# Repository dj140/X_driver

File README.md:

# X_driver
Base on odrive 3.5 sch

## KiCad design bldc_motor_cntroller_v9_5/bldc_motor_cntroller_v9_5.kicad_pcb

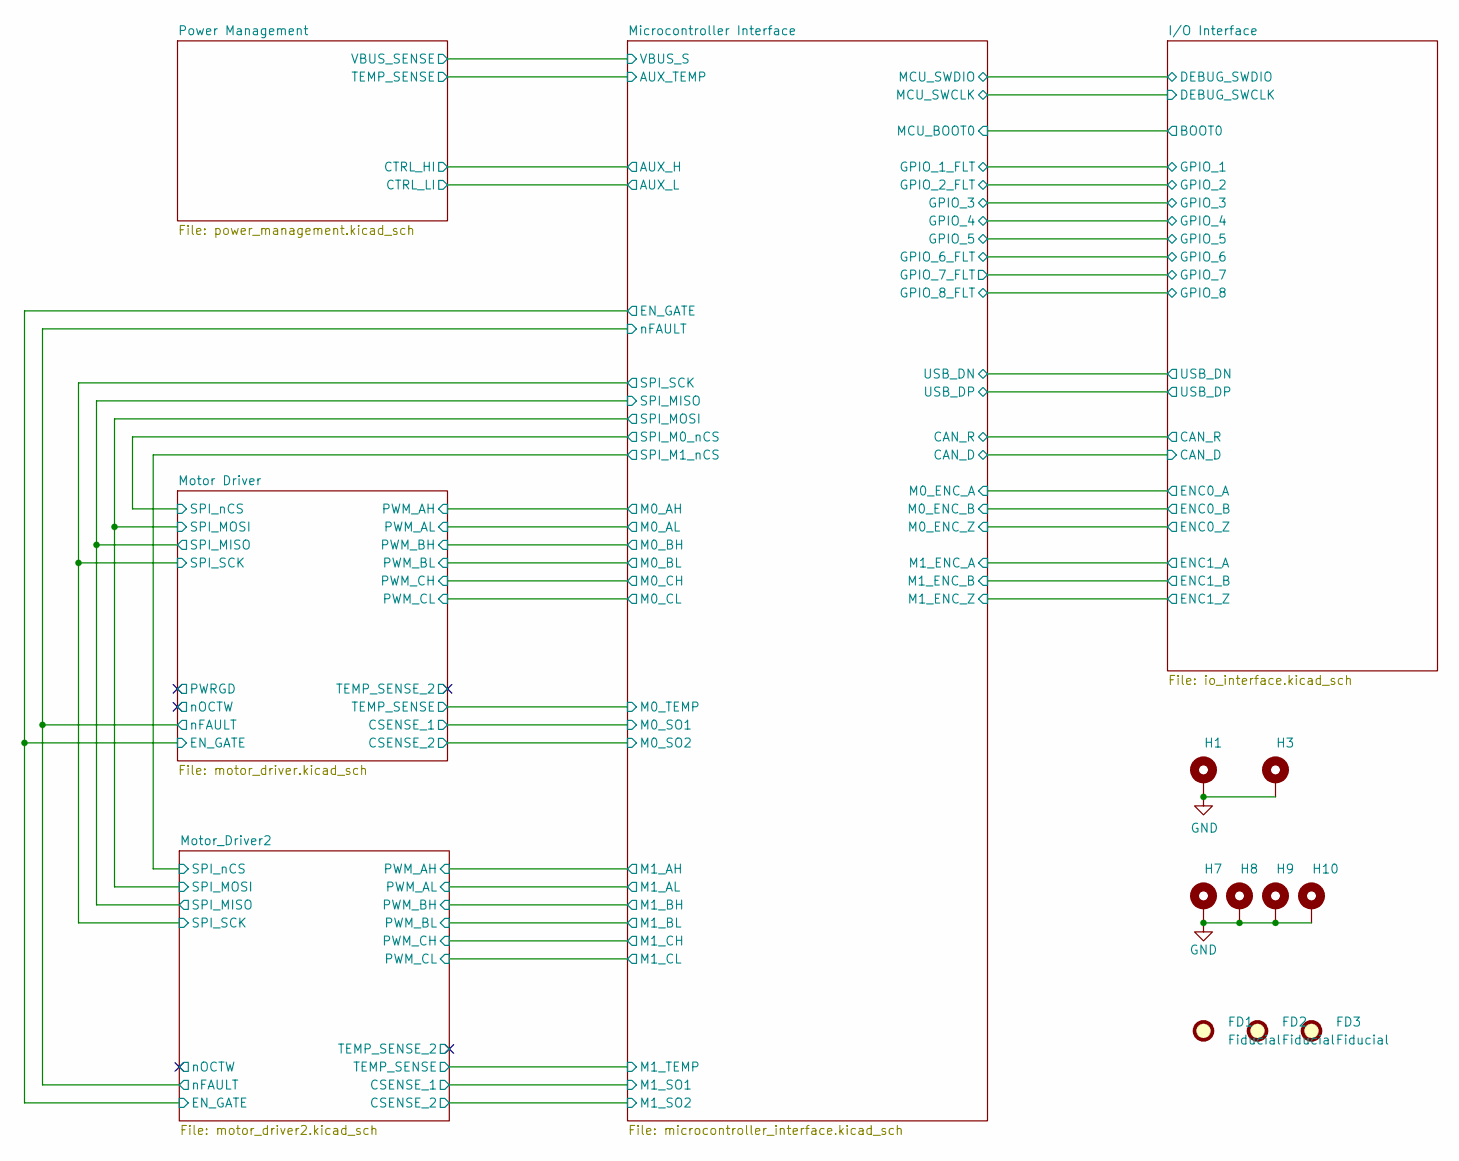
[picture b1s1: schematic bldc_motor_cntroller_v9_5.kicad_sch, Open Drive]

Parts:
FD1, FD2, FD3: Fiducial; Fiducial_1mm_Mask2mm
H1, H3: MountingHole_3.2mm_M3_Pad_Via
H7, H8, H9, H10: MountingHole_Pad; MountingHole_4.3mm_M4_Pad

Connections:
GND: H1.1, H3.1, H7.1, H8.1, H9.1, H10.1; also elsewhere on the board

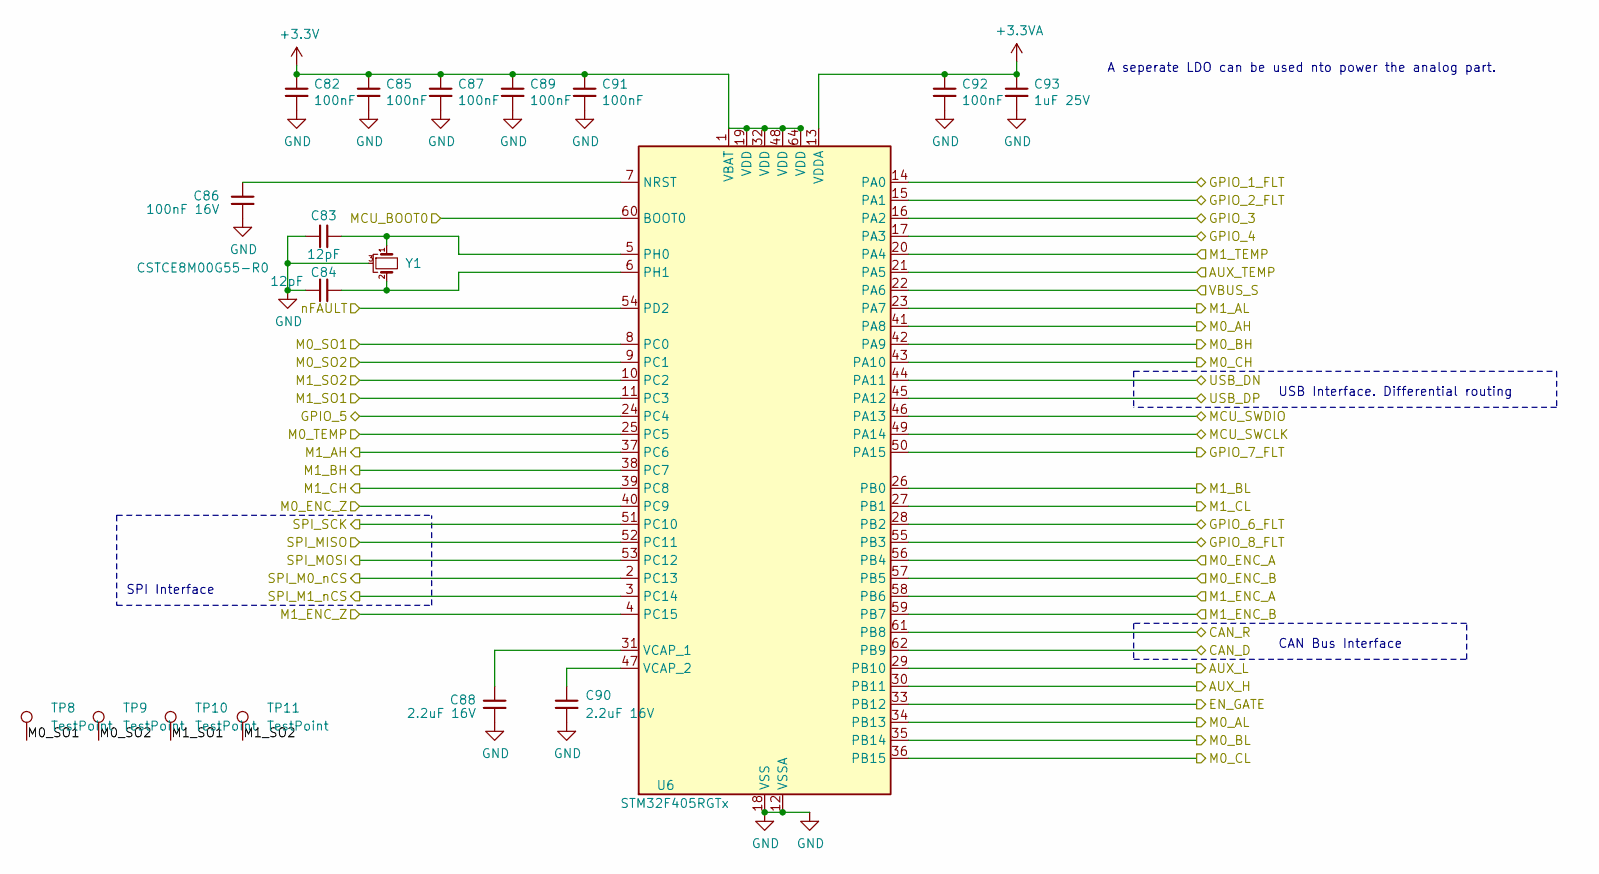
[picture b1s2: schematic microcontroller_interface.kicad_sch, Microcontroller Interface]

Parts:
C82, C85, C87, C89, C91, C92: 100nF; C_0402_1005Metric; MPN GRM155R62A104KE14D; LCSC Part # C1525
C83, C84: 12pF; C_0402_1005Metric; MPN GCQ1555C1H120FB01D; LCSC Part # C1547
C86: 100nF 16V; C_0402_1005Metric; MPN GRM155C81E225KE11D; LCSC Part # C1525
C88, C90: 2.2uF 16V; C_0402_1005Metric; MPN GRM155C81E225KE11D
C93: 1uF 25V; C_0402_1005Metric; MPN GMK105CC6105MV-F; LCSC Part # C52923
TP8, TP9, TP10, TP11: TestPoint; TestPoint_Pad_D1.0mm
U6: STM32F405RGTx; LQFP-64_10x10mm_P0.5mm; MPN STM32F405RGT7
Y1: CSTCE8M00G55-R0; MPN CSTCE8M00G55-R0

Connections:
+3.3V: C82.1, C85.1, C87.1, C89.1, C91.1, U6.1 (VBAT), U6.19 (VDD), U6.32 (VDD), U6.48 (VDD), U6.64 (VDD); also elsewhere on the board
+3.3VA: C92.1, C93.1, U6.13 (VDDA); also elsewhere on the board
/I/O Interface/BOOT0: U6.60 (BOOT0); also elsewhere on the board
/I/O Interface/CAN_D: U6.62 (PB9); also elsewhere on the board
/I/O Interface/CAN_R: U6.61 (PB8); also elsewhere on the board
/I/O Interface/DEBUG_SWCLK: U6.49 (PA14); also elsewhere on the board
/I/O Interface/DEBUG_SWDIO: U6.46 (PA13); also elsewhere on the board
/I/O Interface/ENC0_A: U6.56 (PB4); also elsewhere on the board
/I/O Interface/ENC0_B: U6.57 (PB5); also elsewhere on the board
/I/O Interface/ENC0_Z: U6.40 (PC9); also elsewhere on the board
/I/O Interface/ENC1_A: U6.58 (PB6); also elsewhere on the board
/I/O Interface/ENC1_B: U6.59 (PB7); also elsewhere on the board
/I/O Interface/ENC1_Z: U6.4 (PC15); also elsewhere on the board
/I/O Interface/GPIO_1: U6.14 (PA0); also elsewhere on the board
/I/O Interface/GPIO_2: U6.15 (PA1); also elsewhere on the board
/I/O Interface/GPIO_3: U6.16 (PA2); also elsewhere on the board
/I/O Interface/GPIO_4: U6.17 (PA3); also elsewhere on the board
/I/O Interface/GPIO_5: U6.24 (PC4); also elsewhere on the board
/I/O Interface/GPIO_6: U6.28 (PB2); also elsewhere on the board
/I/O Interface/GPIO_7: U6.50 (PA15); also elsewhere on the board
/I/O Interface/GPIO_8: U6.55 (PB3); also elsewhere on the board
/I/O Interface/USB_DN: U6.44 (PA11); also elsewhere on the board
/I/O Interface/USB_DP: U6.45 (PA12); also elsewhere on the board
/Microcontroller Interface/AUX_H: U6.30 (PB11); also elsewhere on the board
/Microcontroller Interface/AUX_L: U6.29 (PB10); also elsewhere on the board
/Microcontroller Interface/AUX_TEMP: U6.21 (PA5); also elsewhere on the board
/Microcontroller Interface/EN_GATE: U6.33 (PB12); also elsewhere on the board
/Microcontroller Interface/M0_AH: U6.41 (PA8); also elsewhere on the board
/Microcontroller Interface/M0_AL: U6.34 (PB13); also elsewhere on the board
/Microcontroller Interface/M0_BH: U6.42 (PA9); also elsewhere on the board
/Microcontroller Interface/M0_BL: U6.35 (PB14); also elsewhere on the board
/Microcontroller Interface/M0_CH: U6.43 (PA10); also elsewhere on the board
/Microcontroller Interface/M0_CL: U6.36 (PB15); also elsewhere on the board
/Microcontroller Interface/M0_SO1: TP8.1, U6.8 (PC0); also elsewhere on the board
/Microcontroller Interface/M0_SO2: TP9.1, U6.9 (PC1); also elsewhere on the board
/Microcontroller Interface/M0_TEMP: U6.25 (PC5); also elsewhere on the board
/Microcontroller Interface/M1_AH: U6.37 (PC6); also elsewhere on the board
/Microcontroller Interface/M1_AL: U6.23 (PA7); also elsewhere on the board
/Microcontroller Interface/M1_BH: U6.38 (PC7); also elsewhere on the board
/Microcontroller Interface/M1_BL: U6.26 (PB0); also elsewhere on the board
/Microcontroller Interface/M1_CH: U6.39 (PC8); also elsewhere on the board
/Microcontroller Interface/M1_CL: U6.27 (PB1); also elsewhere on the board
/Microcontroller Interface/M1_SO1: TP10.1, U6.11 (PC3); also elsewhere on the board
/Microcontroller Interface/M1_SO2: TP11.1, U6.10 (PC2); also elsewhere on the board
/Microcontroller Interface/M1_TEMP: U6.20 (PA4); also elsewhere on the board
/Microcontroller Interface/SPI_M0_nCS: U6.2 (PC13); also elsewhere on the board
/Microcontroller Interface/SPI_M1_nCS: U6.3 (PC14); also elsewhere on the board
/Microcontroller Interface/SPI_MISO: U6.52 (PC11); also elsewhere on the board
/Microcontroller Interface/SPI_MOSI: U6.53 (PC12); also elsewhere on the board
/Microcontroller Interface/SPI_SCK: U6.51 (PC10); also elsewhere on the board
/Microcontroller Interface/VBUS_S: U6.22 (PA6); also elsewhere on the board
/Microcontroller Interface/nFAULT: U6.54 (PD2); also elsewhere on the board
GND: C82.2, C83.1, C84.1, C85.2, C86.2, C87.2, C88.2, C89.2, C90.2, C91.2, C92.2, C93.2, U6.12 (VSSA), U6.18 (VSS), U6.63 (VSS), Y1.3; also elsewhere on the board
unnamed: C86.1, U6.7 (NRST)
unnamed: C83.2, U6.5 (PH0), Y1.1
unnamed: C84.2, U6.6 (PH1), Y1.2
unnamed: C88.1, U6.31 (VCAP_1)
unnamed: C90.1, U6.47 (VCAP_2)

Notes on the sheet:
CAN Bus Interface
USB Interface. Differential routing
SPI Interface
A seperate LDO can be used nto power the analog part.

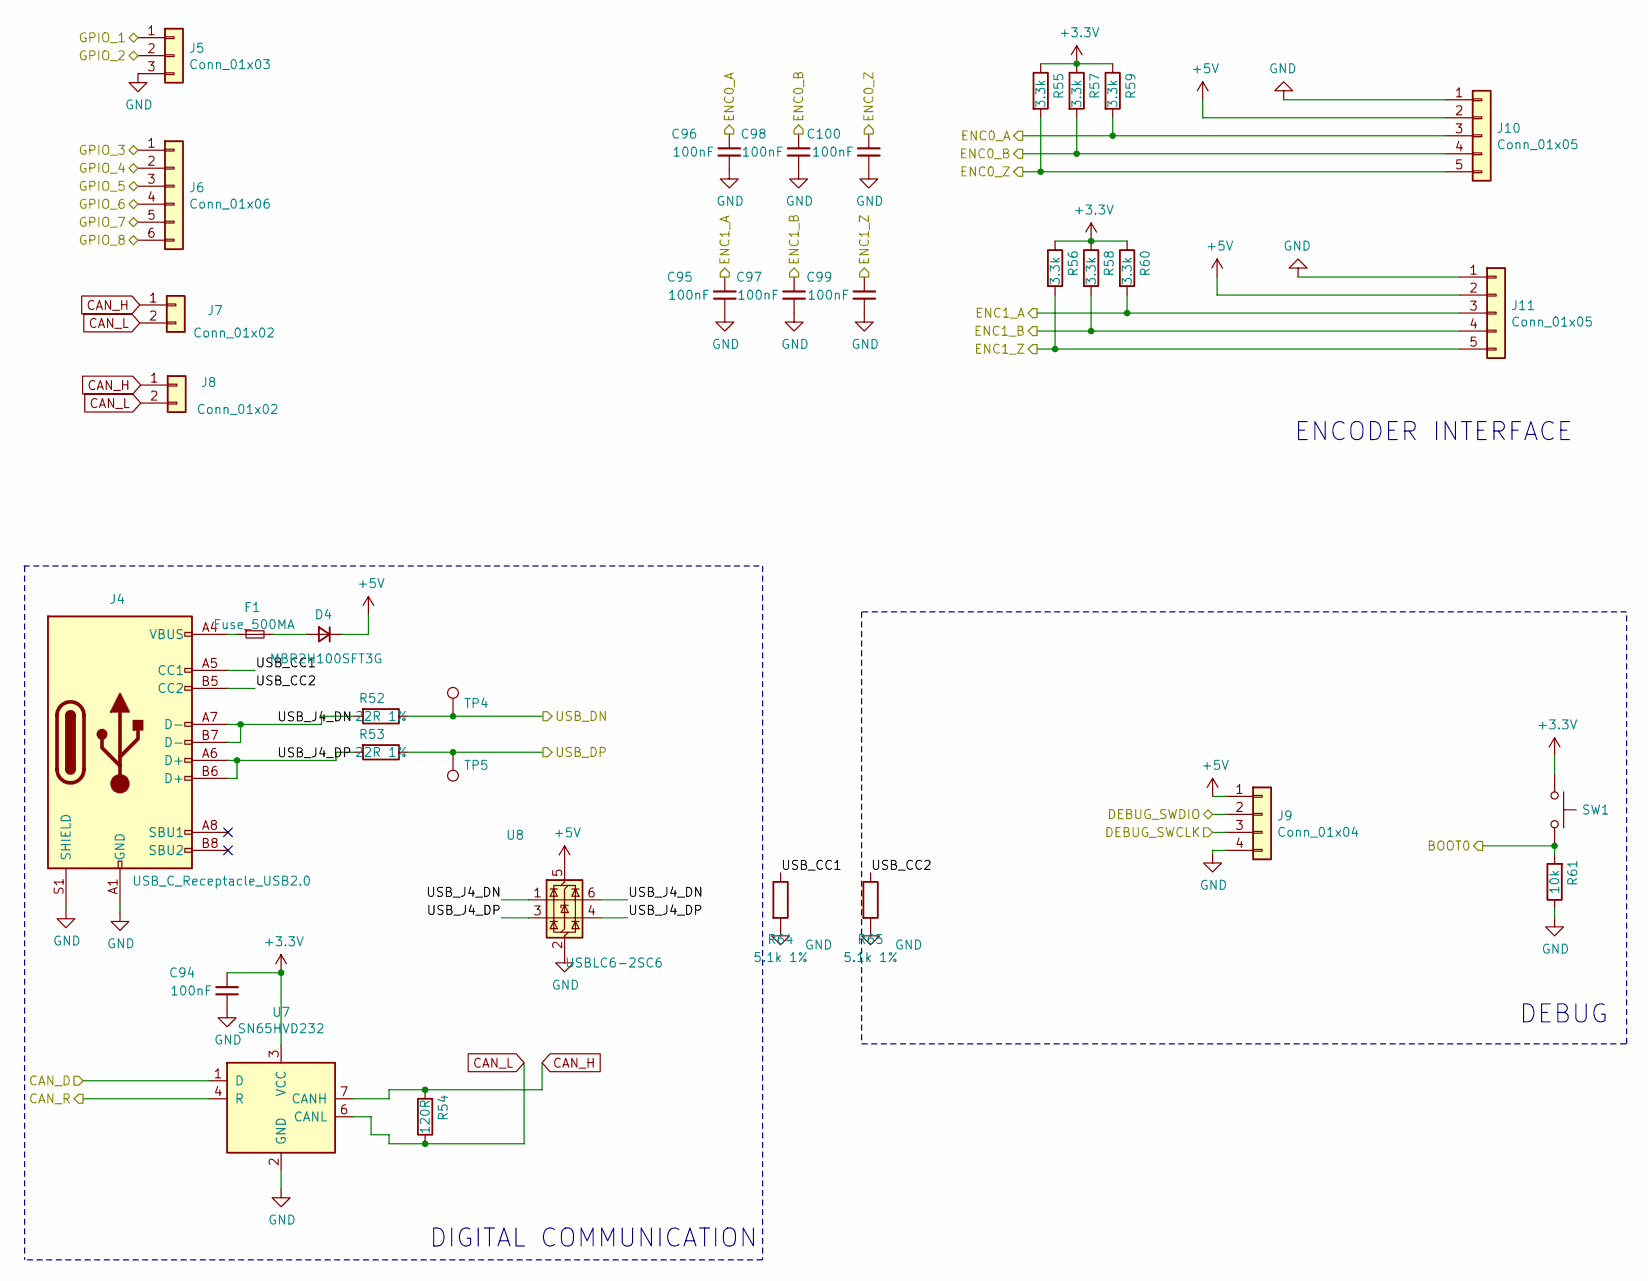
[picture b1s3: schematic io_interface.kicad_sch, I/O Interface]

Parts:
C94, C95, C96, C97, C98, C99, C100: 100nF; C_0402_1005Metric; MPN GRM155R62A104KE14D; LCSC Part # C1525
D4: MBR2H100SFT3G; D_SOD-123F
F1: Fuse_500MA; Fuse_1206_3216Metric
J4: USB_C_Receptacle_USB2.0; USB_C_Receptacle_HRO_TYPE-C-31-M-12
J5: Conn_01x03; JST_SH_SM03B-SRSS-TB_1x03-1MP_P1.00mm_Horizontal
J6: Conn_01x06; JST_SH_SM06B-SRSS-TB_1x06-1MP_P1.00mm_Horizontal
J7, J8: Conn_01x02; JST_SH_SM02B-SRSS-TB_1x02-1MP_P1.00mm_Horizontal
J9: Conn_01x04; JST_SH_SM04B-SRSS-TB_1x04-1MP_P1.00mm_Horizontal
J10, J11: Conn_01x05; JST_SH_SM05B-SRSS-TB_1x05-1MP_P1.00mm_Horizontal
R52, R53: 22R 1%; R_0402_1005Metric; MPN CRCW040222R0FKEDC; LCSC Part # C25092
R54: 120R; R_0402_1005Metric; MPN ERJ-2RKF1200X; LCSC Part # C25079
R55, R56, R57, R58, R59, R60: 3.3k; R_0402_1005Metric; MPN CRCW04023K30FKEDC; LCSC Part # C25890
R61: 10k; R_0402_1005Metric; MPN CRCW040210K0FKEDC; LCSC Part # C25744
R64, R65: 5.1k 1%; R_0402_1005Metric; MPN CRCW04025K10FKED
SW1: B3U-1000P-B; SW_SPST_B3U-1000P; MPN B3U-1000P-B
TP4, TP5: TestPoint; TestPoint_Pad_D1.0mm
U7: SN65HVD232; SOIC-8_3.9x4.9mm_P1.27mm
U8: USBLC6-2SC6; SOT-23-6

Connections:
+3.3V: C94.2, R55.1, R56.1, R57.1, R58.1, R59.1, R60.1, SW1.1, U7.3 (VCC); also elsewhere on the board
+5V: D4.1 (K), J9.1, J10.2, J11.2, U8.5 (VBUS); also elsewhere on the board
/I/O Interface/BOOT0: R61.2, SW1.2; also elsewhere on the board
/I/O Interface/CAN_D: U7.1 (D); also elsewhere on the board
/I/O Interface/CAN_R: U7.4 (R); also elsewhere on the board
/I/O Interface/DEBUG_SWCLK: J9.3; also elsewhere on the board
/I/O Interface/DEBUG_SWDIO: J9.2; also elsewhere on the board
/I/O Interface/ENC0_A: C96.2, J10.3, R59.2; also elsewhere on the board
/I/O Interface/ENC0_B: C98.2, J10.4, R57.2; also elsewhere on the board
/I/O Interface/ENC0_Z: C100.2, J10.5, R55.2; also elsewhere on the board
/I/O Interface/ENC1_A: C95.2, J11.3, R60.2; also elsewhere on the board
/I/O Interface/ENC1_B: C97.2, J11.4, R58.2; also elsewhere on the board
/I/O Interface/ENC1_Z: C99.2, J11.5, R56.2; also elsewhere on the board
/I/O Interface/GPIO_1: J5.1; also elsewhere on the board
/I/O Interface/GPIO_2: J5.2; also elsewhere on the board
/I/O Interface/GPIO_3: J6.1; also elsewhere on the board
/I/O Interface/GPIO_4: J6.2; also elsewhere on the board
/I/O Interface/GPIO_5: J6.3; also elsewhere on the board
/I/O Interface/GPIO_6: J6.4; also elsewhere on the board
/I/O Interface/GPIO_7: J6.5; also elsewhere on the board
/I/O Interface/GPIO_8: J6.6; also elsewhere on the board
/I/O Interface/USB_CC1: J4.A5 (CC1), R64.1
/I/O Interface/USB_CC2: J4.B5 (CC2), R65.1
/I/O Interface/USB_DN: R52.1, TP4.1; also elsewhere on the board
/I/O Interface/USB_DP: R53.1, TP5.1; also elsewhere on the board
/I/O Interface/USB_J4_DN: J4.A7 (D-), J4.B7 (D-), R52.2, U8.1 (I/O1), U8.6 (I/O1)
/I/O Interface/USB_J4_DP: J4.A6 (D+), J4.B6 (D+), R53.2, U8.3 (I/O2), U8.4 (I/O2)
CAN_H: J7.1, J8.1, R54.2, U7.7 (CANH)
CAN_L: J7.2, J8.2, R54.1, U7.6 (CANL)
GND: C94.1, C95.1, C96.1, C97.1, C98.1, C99.1, C100.1, J4.A1 (GND), J4.A12 (GND), J4.B1 (GND), J4.B12 (GND), J4.S1 (SHIELD), J5.3, J9.4, J10.1, J11.1, R61.1, R64.2, R65.2, U7.2 (GND), U8.2 (GND); also elsewhere on the board
unnamed: D4.2 (A), F1.2
unnamed: F1.1, J4.A4 (VBUS), J4.A9 (VBUS), J4.B4 (VBUS), J4.B9 (VBUS)

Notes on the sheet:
DIGITAL COMMUNICATION
ENCODER INTERFACE
DEBUG

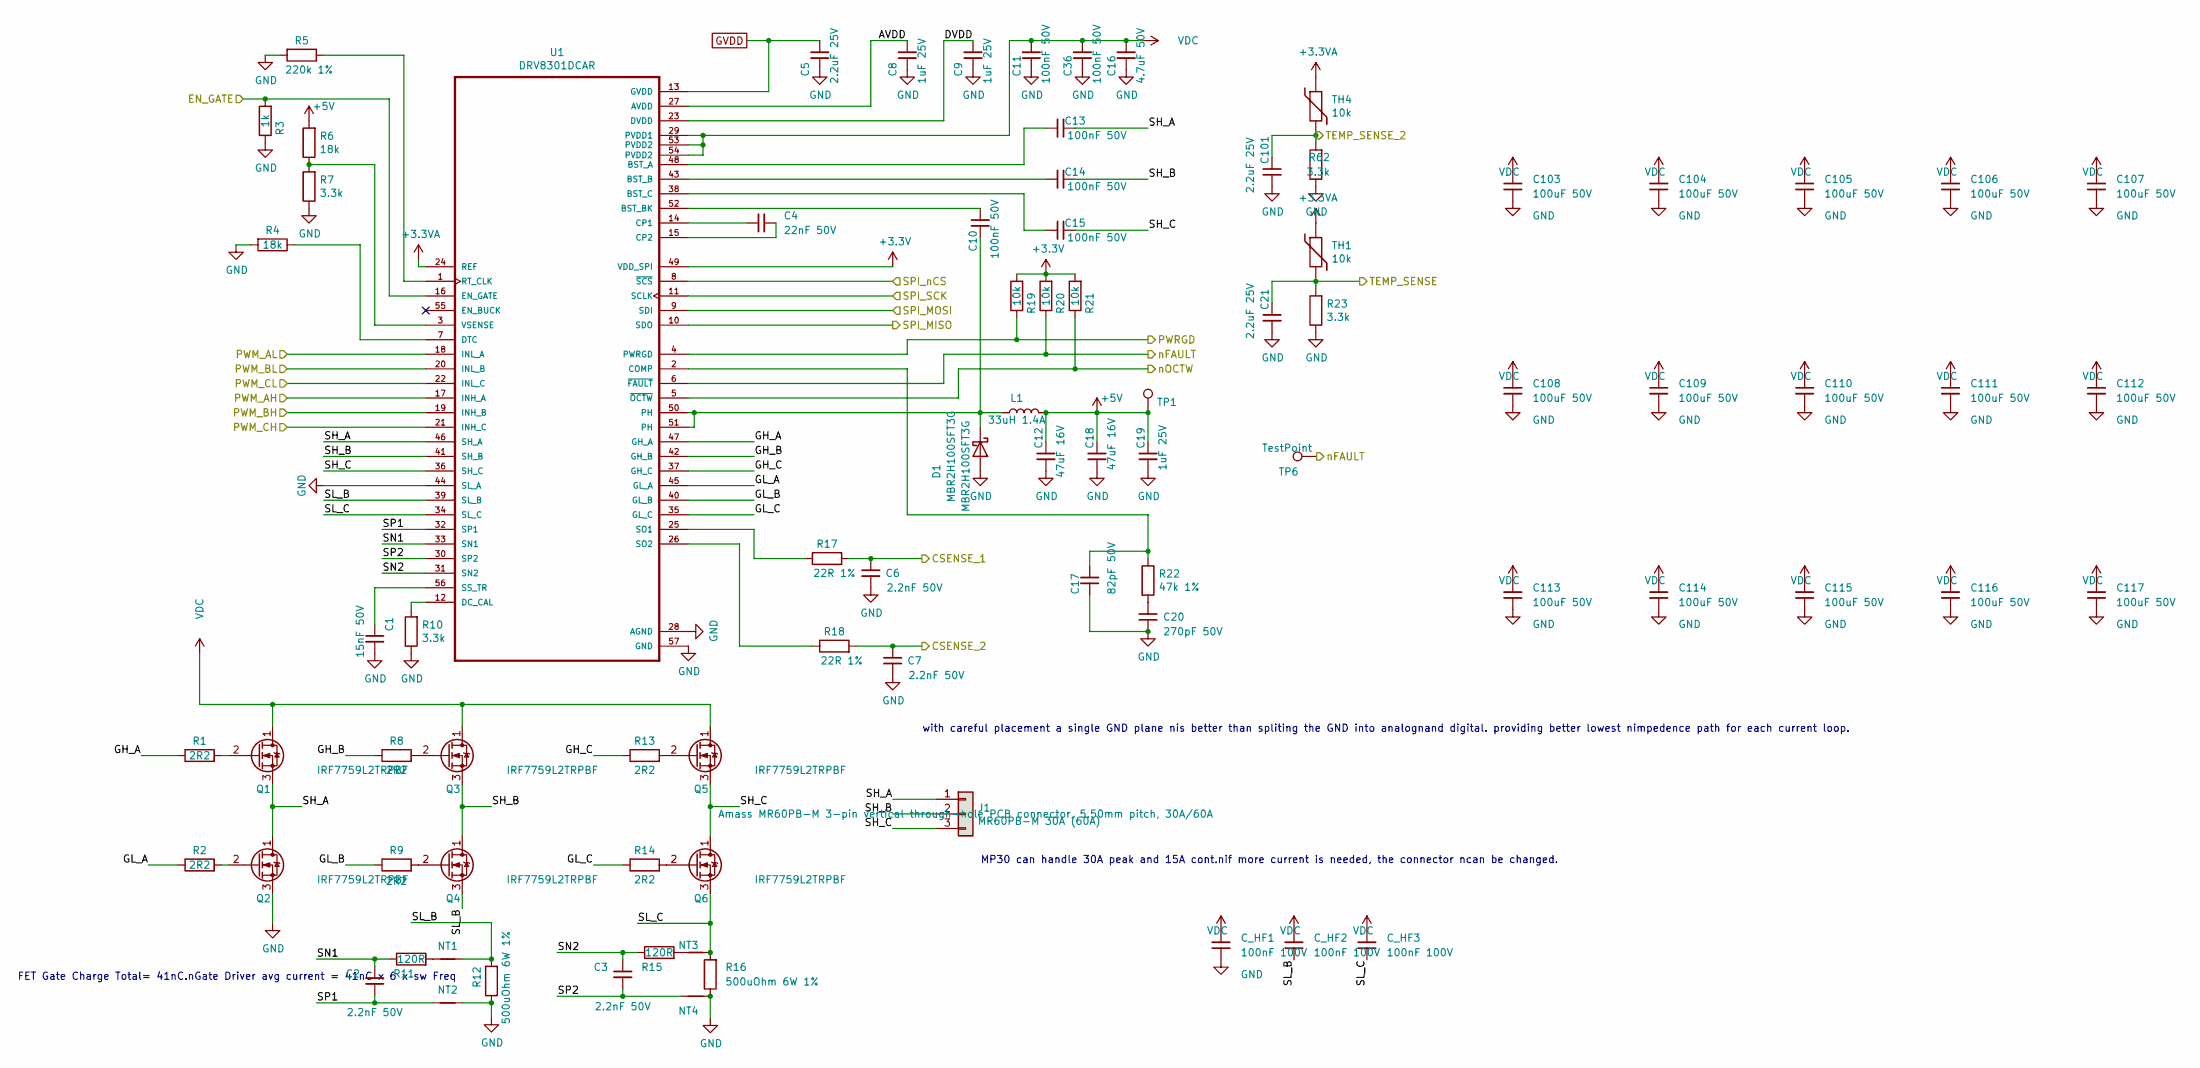
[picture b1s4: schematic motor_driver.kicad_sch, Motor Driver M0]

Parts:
C1: 15nF 50V; C_0402_1005Metric; MPN GCM155R71E153JA55D
C2, C3, C6, C7: 2.2nF 50V; C_0402_1005Metric; MPN C0402C222J3GEC7411; LCSC Part # C1531
C4: 22nF 50V; C_0402_1005Metric; MPN C0402C223K5REC7411; LCSC Part # C1532
C5, C21, C101: 2.2uF 25V; C_0402_1005Metric; MPN GRM155C81E225KE11D; LCSC Part # C12530
C8, C9, C19: 1uF 25V; C_0402_1005Metric; MPN GMK105CC6105MV-F; LCSC Part # C52923
C10, C13, C14, C15: 100nF 50V; C_0402_1005Metric; MPN GCM155L8EH104KE07D
C11, C36: 100nF 50V; C_0402_1005Metric; MPN GRM155R62A104KE14D
C12, C18: 47uF 16V; C_1206_3216Metric; MPN GRM32EC81C476KE15L; LCSC Part # C96123
C16: 4.7uF 50V; C_1206_3216Metric; MPN HMK325C7475KN-TE
C17: 82pF 50V; C_0402_1005Metric; MPN VJ0402A820JXACW1BC
C20: 270pF 50V; C_0402_1005Metric; MPN GRM1555C1H271FA01D
C103, C104, C105, C106, C107, C108, C109, C110, C111, C112, C113, C114, C115, C116, C117: 100uF 50V; C_1206_3216Metric; MPN GMK105CC6105MV-F
C_HF1, C_HF2, C_HF3: 100nF 100V; C_0603_1608Metric; MPN GCM188R72A104KA64D
D1: MBR2H100SFT3G; D_SOD-123F; MPN MBR2H100SFT3G
J1: MR60PB-M 30A (60A); AMASS_MR60PB-M_1x03_P5.50mm_Vertical; MPN MR60PB-M
L1: 33uH 1.4A; L_Taiyo-Yuden_NR-60xx; MPN NR6045T330M
NT1, NT2, NT3, NT4: Net-Tie_2; NetTie-2_SMD_Pad0.5mm
Q1, Q2, Q3, Q4, Q5, Q6: IRF7759L2TRPBF; DirectFET_L8; MPN IRF7759L2TRPBF; LCSC C520641
R1, R2, R8, R9, R13, R14: 2R2; R_0402_1005Metric; MPN CRCW04022R20FKEDC
R3: 1k; R_0402_1005Metric; MPN ERJ-2RKF1001X; LCSC Part # C11702
R4, R6: 18k; R_0402_1005Metric; MPN CRCW040218K0FKED; LCSC Part # C25762
R5: 220k 1%; R_0402_1005Metric; MPN CRCW0402220KFKEDC; LCSC Part # C25767
R7, R10, R23, R62: 3.3k; R_0402_1005Metric; MPN CRCW04023K30FKEDC; LCSC Part # C25890
R11, R15: 120R; R_0402_1005Metric; MPN ERJ-2RKF1200X; LCSC Part # C25079
R12, R16: 500uOhm 6W 1%; R_2512_6332Metric; MPN CSS2H-2512R-L500F
R17, R18: 22R 1%; R_0402_1005Metric; MPN CRCW040222R0FKEDC; LCSC Part # C25092
R19, R20, R21: 10k; R_0402_1005Metric; MPN CRCW040210K0FKEDC; LCSC Part # C25744
R22: 47k 1%; R_0402_1005Metric; MPN CRGP0402F47K; LCSC Part # C25792
TH1, TH4: 10k; R_0402_1005Metric; MPN CRCW040210K0FKEDC
TP1, TP6: TestPoint; TestPoint_Pad_D1.0mm
U1: DRV8301DCAR; DRV8301DCA_v9; MPN DRV8301DCAR

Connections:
+3.3V: R19.2, R20.2, R21.2, U1.49 (VDD_SPI); also elsewhere on the board
+3.3VA: TH1.1, TH4.1, U1.24 (REF); also elsewhere on the board
+5V: C12.1, C18.1, C19.1, L1.2, R6.2, TP1.1; also elsewhere on the board
/Microcontroller Interface/EN_GATE: R3.2, U1.16 (EN_GATE); also elsewhere on the board
/Microcontroller Interface/M0_AH: U1.17 (INH_A); also elsewhere on the board
/Microcontroller Interface/M0_AL: U1.18 (INL_A); also elsewhere on the board
/Microcontroller Interface/M0_BH: U1.19 (INH_B); also elsewhere on the board
/Microcontroller Interface/M0_BL: U1.20 (INL_B); also elsewhere on the board
/Microcontroller Interface/M0_CH: U1.21 (INH_C); also elsewhere on the board
/Microcontroller Interface/M0_CL: U1.22 (INL_C); also elsewhere on the board
/Microcontroller Interface/M0_SO1: C6.2, R17.2; also elsewhere on the board
/Microcontroller Interface/M0_SO2: C7.2, R18.2; also elsewhere on the board
/Microcontroller Interface/M0_TEMP: C21.1, R23.2, TH1.2; also elsewhere on the board
/Microcontroller Interface/SPI_M0_nCS: U1.8 (~SCS); also elsewhere on the board
/Microcontroller Interface/SPI_MISO: U1.10 (SDO); also elsewhere on the board
/Microcontroller Interface/SPI_MOSI: U1.9 (SDI); also elsewhere on the board
/Microcontroller Interface/SPI_SCK: U1.11 (SCLK); also elsewhere on the board
/Microcontroller Interface/nFAULT: R20.1, TP6.1, U1.6 (~FAULT); also elsewhere on the board
/Motor Driver/AVDD: C8.1, U1.27 (AVDD)
/Motor Driver/DVDD: C9.1, U1.23 (DVDD)
/Motor Driver/GH_A: R1.1, U1.47 (GH_A)
/Motor Driver/GH_B: R8.1, U1.42 (GH_B)
/Motor Driver/GH_C: R13.1, U1.37 (GH_C)
/Motor Driver/GL_A: R2.1, U1.45 (GL_A)
/Motor Driver/GL_B: R9.1, U1.40 (GL_B)
/Motor Driver/GL_C: R14.1, U1.35 (GL_C)
/Motor Driver/PWRGD: R19.1, U1.4 (PWRGD)
/Motor Driver/SH_A: C13.1, J1.1, Q1.3 (S), Q2.1 (D), U1.46 (SH_A)
/Motor Driver/SH_B: C14.1, J1.2, Q3.3 (S), Q4.1 (D), U1.41 (SH_B)
/Motor Driver/SH_C: C15.1, J1.3, Q5.3 (S), Q6.1 (D), U1.36 (SH_C)
/Motor Driver/SL_B: C_HF2.2, NT1.2, Q4.3 (S), R12.2, U1.39 (SL_B)
/Motor Driver/SL_C: C_HF3.2, NT3.2, Q6.3 (S), R16.2, U1.34 (SL_C)
/Motor Driver/SN1: C2.2, R11.1, U1.33 (SN1)
/Motor Driver/SN2: C3.2, R15.1, U1.31 (SN2)
/Motor Driver/SP1: C2.1, NT2.1, U1.32 (SP1)
/Motor Driver/SP2: C3.1, NT4.1, U1.30 (SP2)
/Motor Driver/TEMP_SENSE_2: C101.1, R62.2, TH4.2
/Motor Driver/nOCTW: R21.1, U1.5 (~OCTW)
GND: C1.1, C5.2, C6.1, C7.1, C8.2, C9.2, C11.2, C12.2, C16.2, C17.2, C18.2, C19.2, C20.2, C21.2, C36.2, C101.2, C103.2, C104.2, C105.2, C106.2, C107.2, C108.2, C109.2, C110.2, C111.2, C112.2, C113.2, C114.2, C115.2, C116.2, C117.2, C_HF1.2, D1.2 (A), NT2.2, NT4.2, Q2.3 (S), R3.1, R4.2, R5.2, R7.1, R10.1, R12.1, R16.1, R23.1, R62.1, U1.28 (AGND), U1.44 (SL_A), U1.57 (GND); also elsewhere on the board
GVDD: C5.1, U1.13 (GVDD); also elsewhere on the board
unnamed: C20.1, R22.2
unnamed: C10.1, D1.1 (K), L1.1, U1.50 (PH), U1.51 (PH)
unnamed: NT1.1, R11.2
unnamed: NT3.1, R15.2
unnamed: Q1.2 (G), R1.2
unnamed: Q2.2 (G), R2.2
unnamed: Q3.2 (G), R8.2
unnamed: Q4.2 (G), R9.2
unnamed: Q5.2 (G), R13.2
unnamed: Q6.2 (G), R14.2
unnamed: C13.2, U1.48 (BST_A)
unnamed: C14.2, U1.43 (BST_B)
unnamed: C10.2, U1.52 (BST_BK)
unnamed: C15.2, U1.38 (BST_C)
unnamed: C17.1, R22.1, U1.2 (COMP)
unnamed: C4.1, U1.14 (CP1)
unnamed: C4.2, U1.15 (CP2)
unnamed: R10.2, U1.12 (DC_CAL)
unnamed: R4.1, U1.7 (DTC)
unnamed: R5.1, U1.1 (RT_CLK)
unnamed: R17.1, U1.25 (SO1)
unnamed: R18.1, U1.26 (SO2)
unnamed: C1.2, U1.56 (SS_TR)
unnamed: R6.1, R7.2, U1.3 (VSENSE)
VDC: C11.1, C16.1, C36.1, C103.1, C104.1, C105.1, C106.1, C107.1, C108.1, C109.1, C110.1, C111.1, C112.1, C113.1, C114.1, C115.1, C116.1, C117.1, C_HF1.1, C_HF2.1, C_HF3.1, Q1.1 (D), Q3.1 (D), Q5.1 (D), U1.29 (PVDD1), U1.53 (PVDD2), U1.54 (PVDD2); also elsewhere on the board

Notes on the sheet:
MP30 can handle 30A peak and 15A cont.nif more current is needed, the connector ncan be changed.
FET Gate Charge Total= 41nC.nGate Driver avg current = 41nC x 6 x sw Freq
with careful placement a single GND plane nis better than spliting the GND into analognand digital. providing better lowest nimpedence path for each current loop.

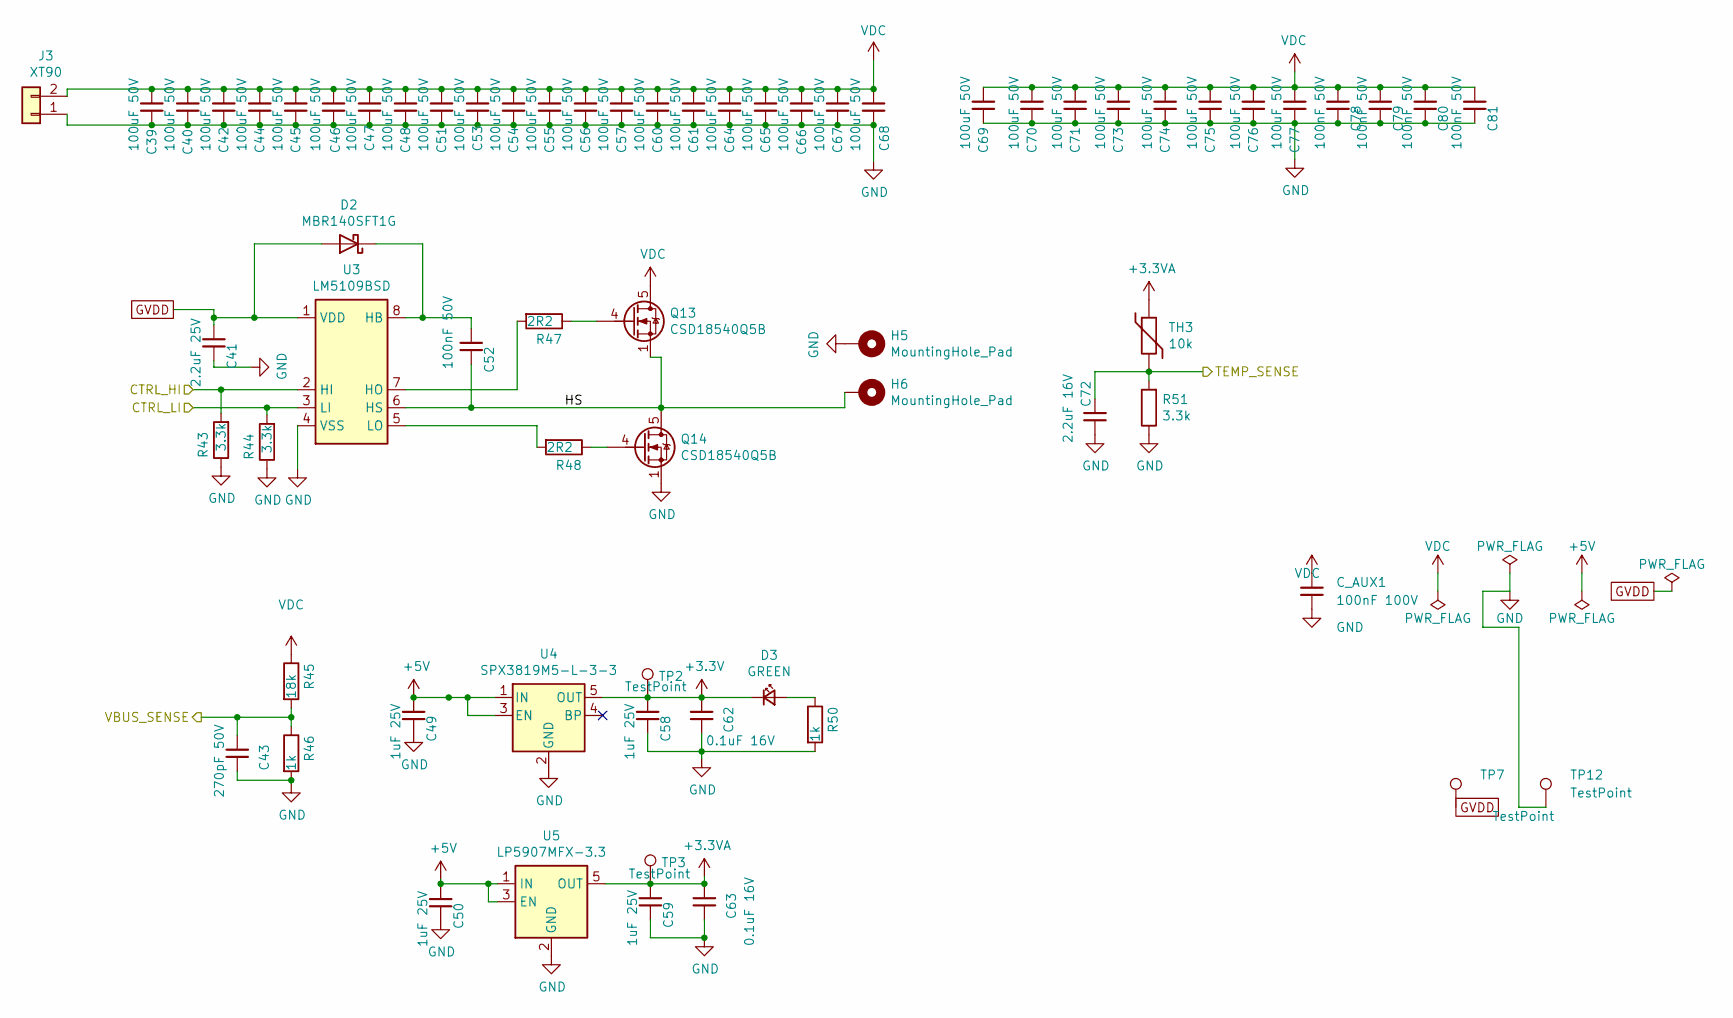
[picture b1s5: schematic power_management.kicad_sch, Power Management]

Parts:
C39, C40, C42, C44, C45, C46, C47, C48, C51, C53, C54, C55, C56, C57, C60, C61, C64, C65, C66, C67, C68, C69, C70, C71, C73, C74, C75, C76, C77: 100uF 50V; C_1206_3216Metric; MPN GMK105CC6105MV-F
C41: 2.2uF 25V; C_0402_1005Metric; MPN GMK105CC6105MV-F; LCSC Part # C12530
C43: 270pF 50V; C_0402_1005Metric; MPN GRM1555C1H271FA01D
C49, C50, C58, C59: 1uF 25V; C_0402_1005Metric; MPN GMK105CC6105MV-F; LCSC Part # C52923
C52: 100nF 50V; C_0402_1005Metric; MPN GMK105CC6105MV-F; LCSC Part # C1525
C62, C63: 0.1uF 16V; C_0402_1005Metric; MPN GRM155R62A104KE14D
C72: 2.2uF 16V; C_0402_1005Metric; MPN GRM155C81E225KE11D; LCSC Part # C12530
C78, C79, C80, C81: 100nF 50V; C_0402_1005Metric; MPN GCM155L8EH104KE07D
C_AUX1: 100nF 100V; C_0603_1608Metric; MPN GCM188R72A104KA64D
D2: MBR140SFT1G; D_SOD-123F
D3: GREEN; LED_0402_1005Metric
H5, H6: MountingHole_Pad; TestPoint_Round
J3: XT90; AMASS_XT90-M_1x02_P10.90mm_Vertical; MPN XT90PB-M
Q13, Q14: CSD18540Q5B; TDSON-8-1
R43, R44: 3.3k; R_0402_1005Metric; MPN CRCW040210K0FKEDC; LCSC Part # C25890
R45: 18k; R_0402_1005Metric; MPN CRCW040210K0FKEDC; LCSC Part # C25762
R46, R50: 1k; R_0402_1005Metric; MPN ERJ-2RKF1001X; LCSC Part # C11702
R47, R48: 2R2; R_0402_1005Metric; MPN CRCW040210K0FKEDC
R51: 3.3k; R_0402_1005Metric; MPN CRCW04023K30FKEDC; LCSC Part # C25890
TH3: 10k; R_0402_1005Metric; MPN CRCW040210K0FKEDC
TP2, TP3, TP7, TP12: TestPoint; TestPoint_Pad_D1.0mm
U3: LM5109BSD; WSON-8_4x4mm_P0.8mm
U4: SPX3819M5-L-3-3; SOT-23-5
U5: LP5907MFX-3.3; SOT-23-5

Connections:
+3.3V: C58.1, C62.1, D3.1 (K), TP2.1, U4.5 (OUT); also elsewhere on the board
+3.3VA: C59.1, C63.1, TH3.1, TP3.1, U5.5 (OUT); also elsewhere on the board
+5V: C49.1, C50.1, U4.1 (IN), U4.3 (EN), U5.1 (IN), U5.3 (EN); also elsewhere on the board
/Microcontroller Interface/AUX_H: R43.2, U3.2 (HI); also elsewhere on the board
/Microcontroller Interface/AUX_L: R44.2, U3.3 (LI); also elsewhere on the board
/Microcontroller Interface/AUX_TEMP: C72.1, R51.2, TH3.2; also elsewhere on the board
/Microcontroller Interface/VBUS_S: C43.1, R45.2, R46.1; also elsewhere on the board
/Power Management/HS: C52.2, H6.1, Q13.1 (S), Q13.2 (S), Q13.3 (S), Q14.5 (D), U3.6 (HS)
GND: C39.2, C40.2, C41.2, C42.2, C43.2, C44.2, C45.2, C46.2, C47.2, C48.2, C49.2, C50.2, C51.2, C53.2, C54.2, C55.2, C56.2, C57.2, C58.2, C59.2, C60.2, C61.2, C62.2, C63.2, C64.2, C65.2, C66.2, C67.2, C68.2, C69.2, C70.2, C71.2, C72.2, C73.2, C74.2, C75.2, C76.2, C77.2, C78.2, C79.2, C80.2, C81.2, C_AUX1.2, H5.1, J3.1, Q14.1 (S), Q14.2 (S), Q14.3 (S), R43.1, R44.1, R46.2, R50.2, R51.1, TP12.1, U3.4 (VSS), U3.9 (VSS), U4.2 (GND), U5.2 (GND); also elsewhere on the board
GVDD: C41.1, D2.2 (A), TP7.1, U3.1 (VDD); also elsewhere on the board
unnamed: C52.1, D2.1 (K), U3.8 (HB)
unnamed: D3.2 (A), R50.1
unnamed: Q13.4 (G), R47.1
unnamed: Q14.4 (G), R48.1
unnamed: R47.2, U3.7 (HO)
unnamed: R48.2, U3.5 (LO)
VDC: C39.1, C40.1, C42.1, C44.1, C45.1, C46.1, C47.1, C48.1, C51.1, C53.1, C54.1, C55.1, C56.1, C57.1, C60.1, C61.1, C64.1, C65.1, C66.1, C67.1, C68.1, C69.1, C70.1, C71.1, C73.1, C74.1, C75.1, C76.1, C77.1, C78.1, C79.1, C80.1, C81.1, C_AUX1.1, J3.2, Q13.5 (D), R45.1; also elsewhere on the board
